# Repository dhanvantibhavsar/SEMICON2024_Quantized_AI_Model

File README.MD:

# Quantized AI Model
- Exhibited at :- Semicon 2024 with VSD (VLSI System Design) team
- Presended By :- VLSI System Design
- Duration :- 11 Sep to 13 Sep
- Based on :- Real Time Implementation of Low-Bit Quntized Neural network on Risc-V microcontroller

## Main Features 
- Demonstrates Neural network on VSD Squadron Mini Risc-V development board
- Interfaced  camera with CH32V003F4U6 based microcontroller
- Demonstrates on edge AI capabilities of Risc-V microcontroller
- Complete demonstration implemented on VSD Squadron Mini based on Risc-V microcobtroller

## Demo Video 
https://github.com/user-attachments/assets/e731484d-ab7b-4347-bf47-5b0f53fb8fbb

## Demo kit images

## PCB Design
Please find the complete pcb design structure in [PCB_DESIGN](./PCB_DESIGN/)
Use kicad to open the schematic as well as PCB design. Here is a image of top silk layer

Here is a image of printed PCB with components attached

## Semicon Gallary

## Social Media link
[Media linkedIn Post](https://www.linkedin.com/posts/dhanvanti-bhavsar-387620160_the-india-expo-centre-mart-buzzed-with-activity-7241767522583138305-5wRa?utm_source=share&utm_medium=member_desktop)

[linkedIn Post](https://www.linkedin.com/posts/dhanvanti-bhavsar-387620160_semicon2024-vlsi-riscv-activity-7241765933315174400-G3Z_?utm_source=share&utm_medium=member_desktop)

**Please Check underlying Readme.md files for further details of every task**

## Flow of the QUantized AI Model
1. [Training](./Training/)
2. [Camera Interfacing](./VSD_Camera_Interfacing/)
3. [Prediction](./VSD_Prediction/)

## Circuit diagram
- 

## Project structure
```
SEMICON2024_Quantized_AI_Model

Directory Structure
Below is the complete directory structure of the project:

SEMICON2024_Quantized_AI_Model/
├── images
├── project_root
├── Training
│   ├── a.out
│   ├── BitNetMCU.py
│   ├── BitNetMCUdemo.c
│   ├── BitNetMCU_inference.c
│   ├── BitNetMCU_inference.h
│   ├── BitNetMCU_MNIST_dll.c
│   ├── BitNetMCU_MNIST_test.c
│   ├── BitNetMCU_MNIST_test_data.h
│   ├── BitNetMCU_model.h
│   ├── BitNetMCU_model28.h
│   ├── BitNetMCU_model28x28.h
│   ├── BitNetMCU_model28x28.h.gch
│   ├── BitNetMCU_model_321616.h
│   ├── BitNetMCU_model_643216.h
│   ├── Bitnet_inf.dll
│   ├── exportquant.py
│   ├── Makefile
│   ├── models.py
│   ├── readme.md
│   ├── requirements.txt
│   ├── testoutput.o
│   ├── test_inference.py
│   ├── training.py
│   └── trainingparameters.yaml
│   ├── data
│   │   └── MNIST
│   │       └── raw
│   ├── images
│   ├── modeldata
├── VSD_Camera_Interfacing
│   ├── .gitignore
│   ├── platformio.ini
│   ├── Readme.md
│   ├── .vscode
│   │   └── extensions.json
│   ├── boards
│   │   └── VSDSquadron.json
│   ├── include
│   │   └── README
│   ├── lib
│   │   ├── README
│   │   └── LiveOV7670Library
│   │       ├── CameraOV7670.cpp
│   │       ├── CameraOV7670.h
│   │       ├── CameraOV7670RegisterDefinitions.h
│   │       ├── CameraOV7670Registers.cpp
│   │       ├── CameraOV7670Registers.h
│   │       ├── CameraOV7670RegistersDefault.cpp
│   │       ├── CameraOV7670RegistersQQVGA.cpp
│   │       ├── CameraOV7670RegistersYUV422.cpp
│   │       └── readme.txt
│   ├── src
│   │   ├── main.cpp
│   │   ├── SendUartImageBitNet.cpp
│   │   └── SendUartImageBitNet.h
│   └── test
│       └── README
└── VSD_Prediction
    ├── .gitignore
    ├── platformio.ini
    ├── readme.md
    ├── .vscode
    │   └── extensions.json
    ├── data
    │   ├── BitNetMCU_inference.c
    │   ├── BitNetMCU_inference.h
    │   ├── BitNetMCU_model.h
    │   ├── BitNetMCU_model28.h
    │   ├── BitNetMCU_model28x28.h
    │   ├── BitNetMCU_model_321616.h
    │   └── BitNetMCU_model_643216.h
    ├── include
    │   └── README
    ├── lib
    │   └── README
    ├── src
    │   └── main.c
    └── test
        └── README

```
## Description of Directories

### Root Directory

- *images/*  
  Contains images and videos used for documentation purposes, such as implementation videos, circuit diagrams, dataset visuals, and training snapshots.

- *project_root/*  
  (Currently empty or reserved for future use. Provide details if applicable.)

### Training

- *Training/*  
  Holds all files related to training the neural network model.

  - *data/*
  
    - *MNIST/raw/*  
      Contains raw MNIST dataset files, including images and labels for both training and testing.

  - *modeldata/*  
    Stores trained model files with various configurations and hyperparameters.

  - *runs/*  
    Contains logs and event files for different training runs, useful for tracking experiments and performance.

#### Key Files:
- training.py: Main script for training the model.
- BitNetMCU.py, BitNetMCUdemo.c, etc.: Scripts and source files related to the BitNetMCU implementation.
- Makefile: Build instructions.
- requirements.txt: Python dependencies.
- exportquant.py: Script for exporting quantized models.
- trainingparameters.yaml: Configuration file for training parameters.

### VSD_Camera_Interfacing

- *VSD_Camera_Interfacing/*  
  Contains code and configurations for interfacing the camera with the VSD platform.

  - *.vscode/*  
    VSCode-specific settings and extensions.

  - *boards/*  
    Board configuration files, e.g., VSDSquadron.json.

  - *include/*  
    Header files and additional includes.

  - *lib/*  
    Libraries used in the project, such as the LiveOV7670Library for camera operations.

  - *src/*  
    Source code files handling the main functionality, including image transmission via UART.

  - *test/*  
    Test scripts and documentation for verifying camera interfacing.

#### Key Files:
- platformio.ini: PlatformIO configuration.
- main.cpp: Main application code.
- SendUartImageBitNet.cpp & .h: Code for sending images over UART.

### VSD_Prediction

- *VSD_Prediction/*  
  Contains code and configurations for the prediction module within the VSD platform.

  - *.vscode/*  
    VSCode-specific settings and extensions.

  - *data/*  
    Data files related to the prediction module, including inference and model headers.

  - *include/*  
    Header files and additional includes.

  - *lib/*  
    Libraries used in the prediction module.

  - *src/*  
    Source code files handling the prediction functionality.

  - *test/*  
    Test scripts and documentation for verifying prediction accuracy and performance.

#### Key Files:
- platformio.ini: PlatformIO configuration.
- main.c: Main application code.

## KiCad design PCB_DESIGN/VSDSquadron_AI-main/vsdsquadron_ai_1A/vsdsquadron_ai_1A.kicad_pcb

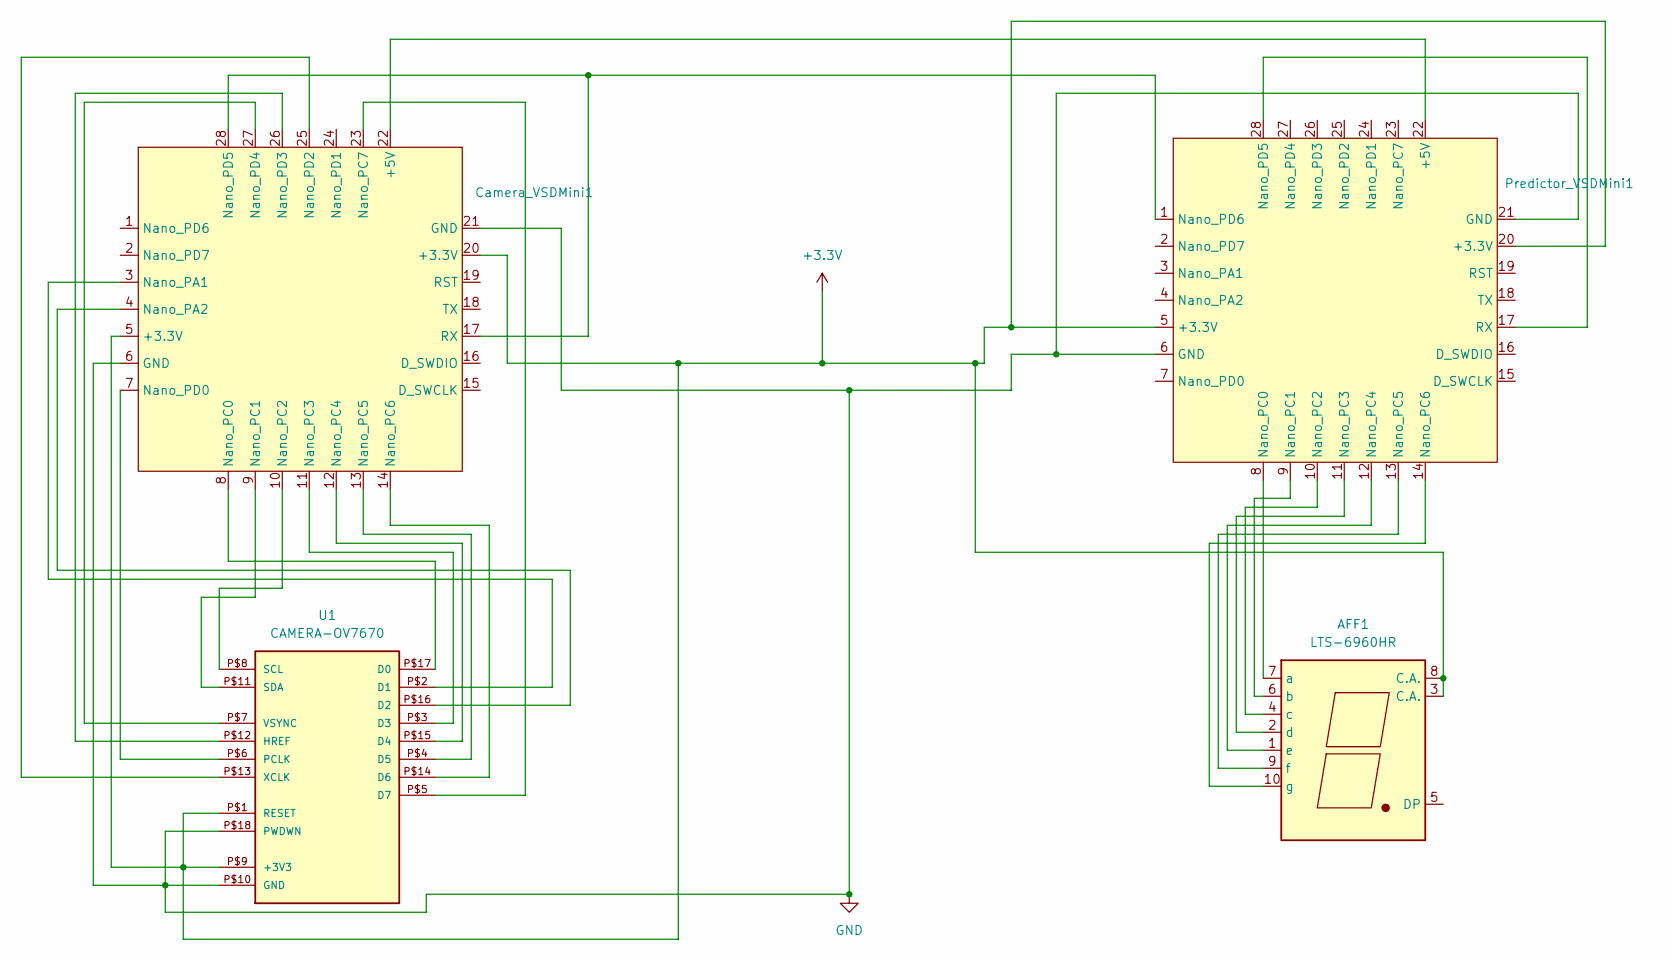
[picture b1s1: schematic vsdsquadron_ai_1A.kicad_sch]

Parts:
AFF1: LTS-6960HR; 7SegmentLED_LTS6760_LTS6780
Camera_VSDMini1: VSDSquadron Mini
Predictor_VSDMini1: VSDSquadron Mini
U1: CAMERA-OV7670; CAMERA-OV7670-DIP

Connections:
+3.3V: AFF1.3 (C.A.), AFF1.8 (C.A.), Camera_VSDMini1.5 (+3.3V), Camera_VSDMini1.20 (+3.3V), Predictor_VSDMini1.5 (+3.3V), Predictor_VSDMini1.20 (+3.3V), U1.P$1 (RESET), U1.P$9 (+3V3)
GND: Camera_VSDMini1.6 (GND), Camera_VSDMini1.21 (GND), Predictor_VSDMini1.6 (GND), Predictor_VSDMini1.21 (GND), U1.P$10 (GND), U1.P$18 (PWDWN)
unnamed: AFF1.7 (a), Predictor_VSDMini1.8 (Nano_PC0)
unnamed: AFF1.6 (b), Predictor_VSDMini1.9 (Nano_PC1)
unnamed: AFF1.4 (c), Predictor_VSDMini1.10 (Nano_PC2)
unnamed: AFF1.2 (d), Predictor_VSDMini1.11 (Nano_PC3)
unnamed: AFF1.1 (e), Predictor_VSDMini1.12 (Nano_PC4)
unnamed: AFF1.9 (f), Predictor_VSDMini1.13 (Nano_PC5)
unnamed: AFF1.10 (g), Predictor_VSDMini1.14 (Nano_PC6)
unnamed: Camera_VSDMini1.22 (+5V), Predictor_VSDMini1.22 (+5V)
unnamed: Camera_VSDMini1.3 (Nano_PA1), U1.P$2 (D1)
unnamed: Camera_VSDMini1.4 (Nano_PA2), U1.P$16 (D2)
unnamed: Camera_VSDMini1.8 (Nano_PC0), U1.P$17 (D0)
unnamed: Camera_VSDMini1.9 (Nano_PC1), U1.P$11 (SDA)
unnamed: Camera_VSDMini1.10 (Nano_PC2), U1.P$8 (SCL)
unnamed: Camera_VSDMini1.11 (Nano_PC3), U1.P$3 (D3)
unnamed: Camera_VSDMini1.12 (Nano_PC4), U1.P$15 (D4)
unnamed: Camera_VSDMini1.13 (Nano_PC5), U1.P$4 (D5)
unnamed: Camera_VSDMini1.14 (Nano_PC6), U1.P$14 (D6)
unnamed: Camera_VSDMini1.23 (Nano_PC7), U1.P$5 (D7)
unnamed: Camera_VSDMini1.7 (Nano_PD0), U1.P$6 (PCLK)
unnamed: Camera_VSDMini1.25 (Nano_PD2), U1.P$13 (XCLK)
unnamed: Camera_VSDMini1.26 (Nano_PD3), U1.P$12 (HREF)
unnamed: Camera_VSDMini1.27 (Nano_PD4), U1.P$7 (VSYNC)
unnamed: Camera_VSDMini1.17 (RX), Camera_VSDMini1.28 (Nano_PD5), Predictor_VSDMini1.1 (Nano_PD6)
unnamed: Predictor_VSDMini1.17 (RX), Predictor_VSDMini1.28 (Nano_PD5)

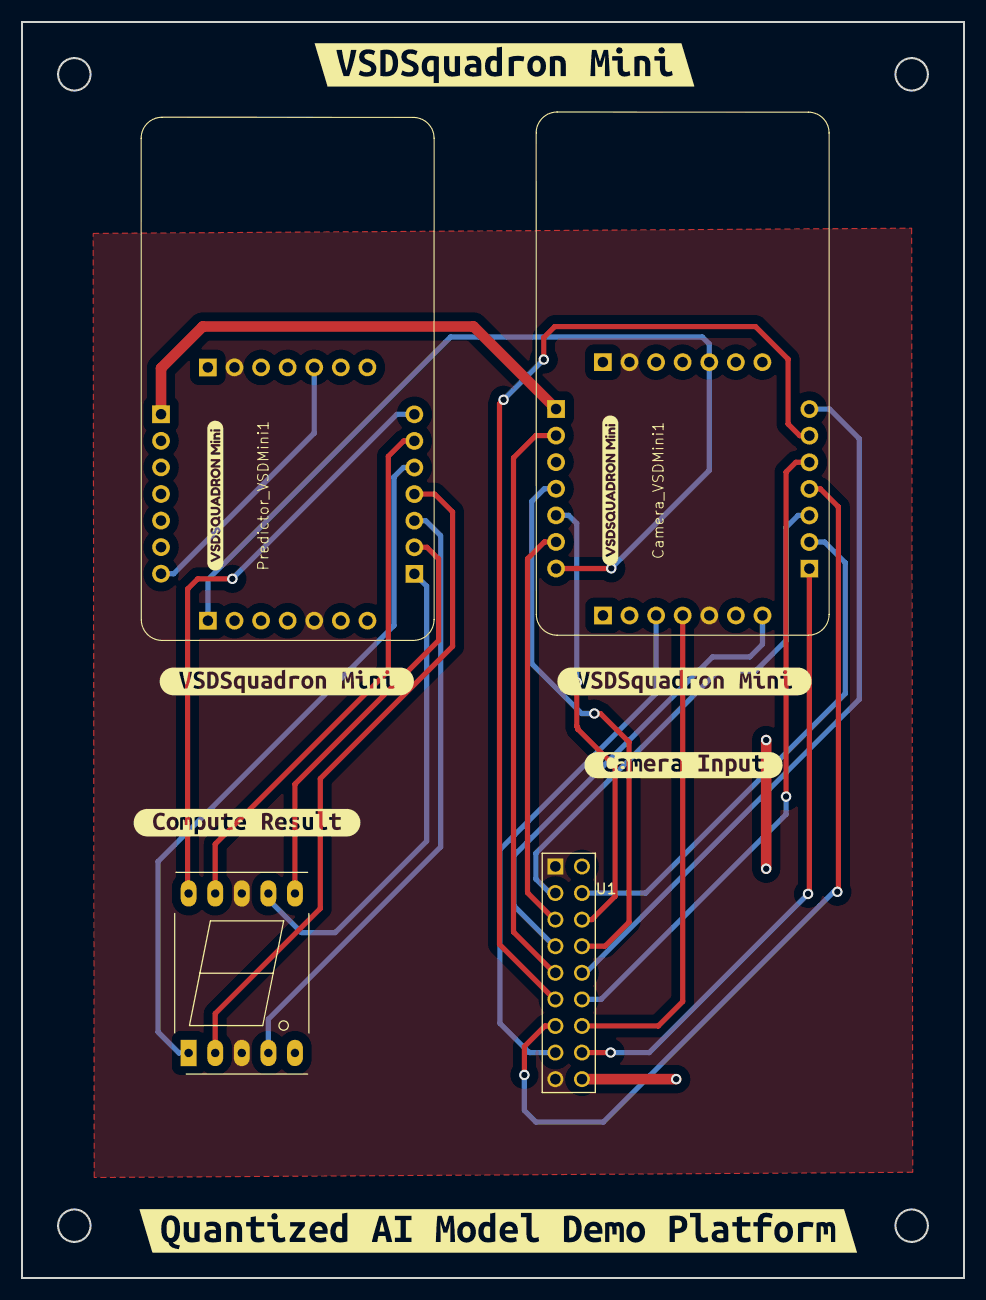
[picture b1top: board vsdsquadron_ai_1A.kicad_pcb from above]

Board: 2 copper layers, 90.0 x 120.0 mm, 10 parts (0 on the bottom side), 26 nets.

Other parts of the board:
kibuzzard-66C8A7E0: G***; kibuzzard-66C8A7E0
kibuzzard-66C8A86F: G***; kibuzzard-66C8A86F
kibuzzard-66C8A791, kibuzzard-66C8A791#2: G***; kibuzzard-66C8A791
kibuzzard-66C8AD7B: G***; kibuzzard-66C8AD7B
kibuzzard-66C8ADA8: G***; kibuzzard-66C8ADA8

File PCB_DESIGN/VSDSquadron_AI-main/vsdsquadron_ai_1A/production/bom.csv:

Designator,Footprint,Quantity,Value,LCSC Part #
AFF1,7SegmentLED_LTS6760_LTS6780,1,LTS-6960HR,
"Camera_VSDMini1, Predictor_VSDMini1",VSDSquadron Mini,2,~,
U1,CAMERA-OV7670-DIP,1,CAMERA-OV7670,

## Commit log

2024-09-25 Mirror Repository
2024-09-25 Updated changes
2024-09-27 uploaded circuit diagram
2024-09-27 updated repo
2024-09-27 added images
2024-09-30 added pcb images
